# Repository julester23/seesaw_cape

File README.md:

# Seesaw 816 to ULN2308 Darlington
8 GPIOs are routed to a ULN2308. It's an easy way to drive 8 relays (up to 30V).

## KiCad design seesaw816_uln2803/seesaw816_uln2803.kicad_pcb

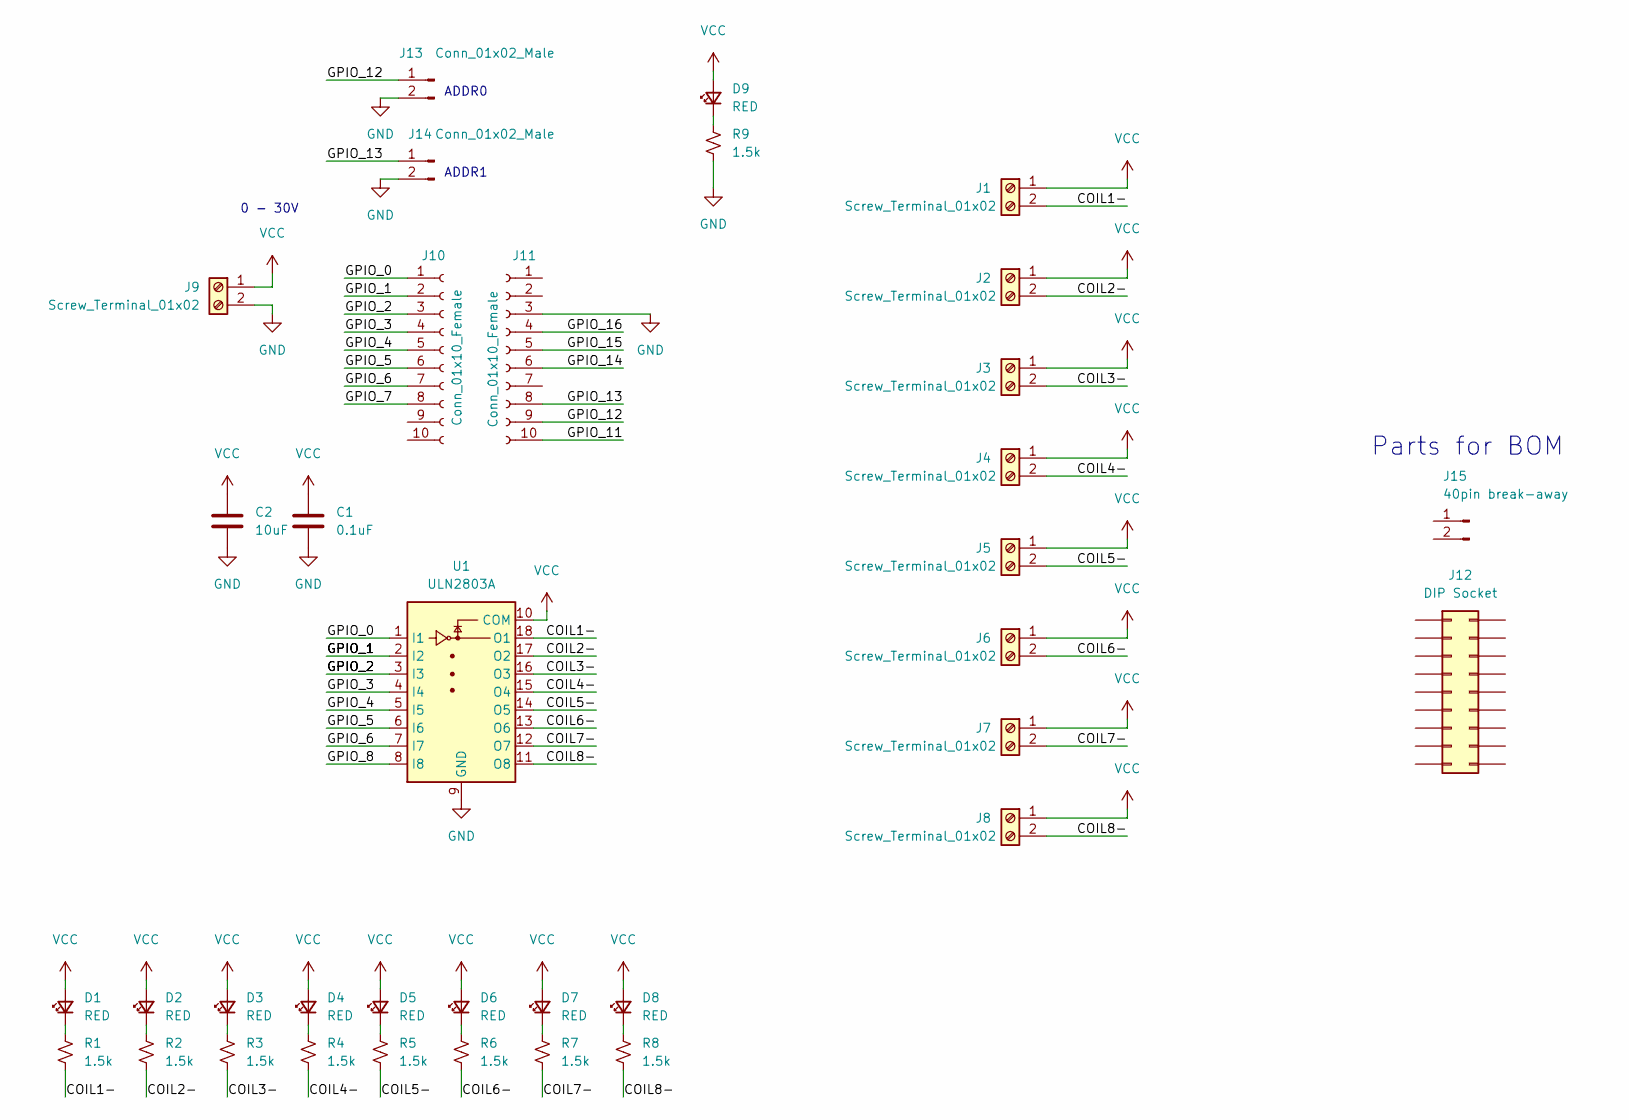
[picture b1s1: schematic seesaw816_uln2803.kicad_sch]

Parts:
C1: 0.1uF; C_0805_2012Metric; Part CC0805KRX7R9BB104
C2: 10uF; CP_Elec_4x5.4; Part EDK106M035A9BAA
D1, D2, D3, D4, D5, D6, D7, D8, D9: RED; LED_0805_2012Metric; Part LS R976-NR-1
J1, J2, J3, J4, J5, J6, J7, J8, J9: Screw_Terminal_01x02; TerminalBlock_TE_282834-2_1x02_P2.54mm_Horizontal
J10, J11: Conn_01x10_Female; PinSocket_1x10_P2.54mm_Vertical
J12: DIP Socket; Part 1-2199298-5
J13, J14: Conn_01x02_Male; PinHeader_1x02_P2.54mm_Vertical
J15: 40pin break-away; Part PRPC040SAAN-RC
R1, R2, R3, R4, R5, R6, R7, R8, R9: 1.5k; R_0805_2012Metric
U1: ULN2803A; DIP-18_W7.62mm_Socket

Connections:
/COIL1-: J1.2, R1.2, U1.18 (O1)
/COIL2-: J2.2, R2.2, U1.17 (O2)
/COIL3-: J3.2, R3.2, U1.16 (O3)
/COIL4-: J4.2, R4.2, U1.15 (O4)
/COIL5-: J5.2, R5.2, U1.14 (O5)
/COIL6-: J6.2, R6.2, U1.13 (O6)
/COIL7-: J7.2, R7.2, U1.12 (O7)
/COIL8-: J8.2, R8.2, U1.11 (O8)
/GPIO_0: J10.1, U1.1 (I1)
/GPIO_1: J10.2, U1.2 (I2)
/GPIO_2: J10.3, U1.3 (I3)
/GPIO_3: J10.4, U1.4 (I4)
/GPIO_4: J10.5, U1.5 (I5)
/GPIO_5: J10.6, U1.6 (I6)
/GPIO_6: J10.7, U1.7 (I7)
/GPIO_7: J10.8
/GPIO_8: U1.8 (I8)
/GPIO_11: J11.10
/GPIO_12: J11.9, J13.1
/GPIO_13: J11.8, J14.1
/GPIO_14: J11.6
/GPIO_15: J11.5
/GPIO_16: J11.4
GND: C1.1, C2.1, J9.2, J11.3, J13.2, J14.2, R9.2, U1.9 (GND)
unnamed: D1.1 (K), R1.1
unnamed: D2.1 (K), R2.1
unnamed: D3.1 (K), R3.1
unnamed: D4.1 (K), R4.1
unnamed: D5.1 (K), R5.1
unnamed: D6.1 (K), R6.1
unnamed: D7.1 (K), R7.1
unnamed: D8.1 (K), R8.1
unnamed: D9.1 (K), R9.1
VCC: C1.2, C2.2, D1.2 (A), D2.2 (A), D3.2 (A), D4.2 (A), D5.2 (A), D6.2 (A), D7.2 (A), D8.2 (A), D9.2 (A), J1.1, J2.1, J3.1, J4.1, J5.1, J6.1, J7.1, J8.1, J9.1, U1.10 (COM)

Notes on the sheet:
0 - 30V
Parts for BOM
ADDR0
ADDR1

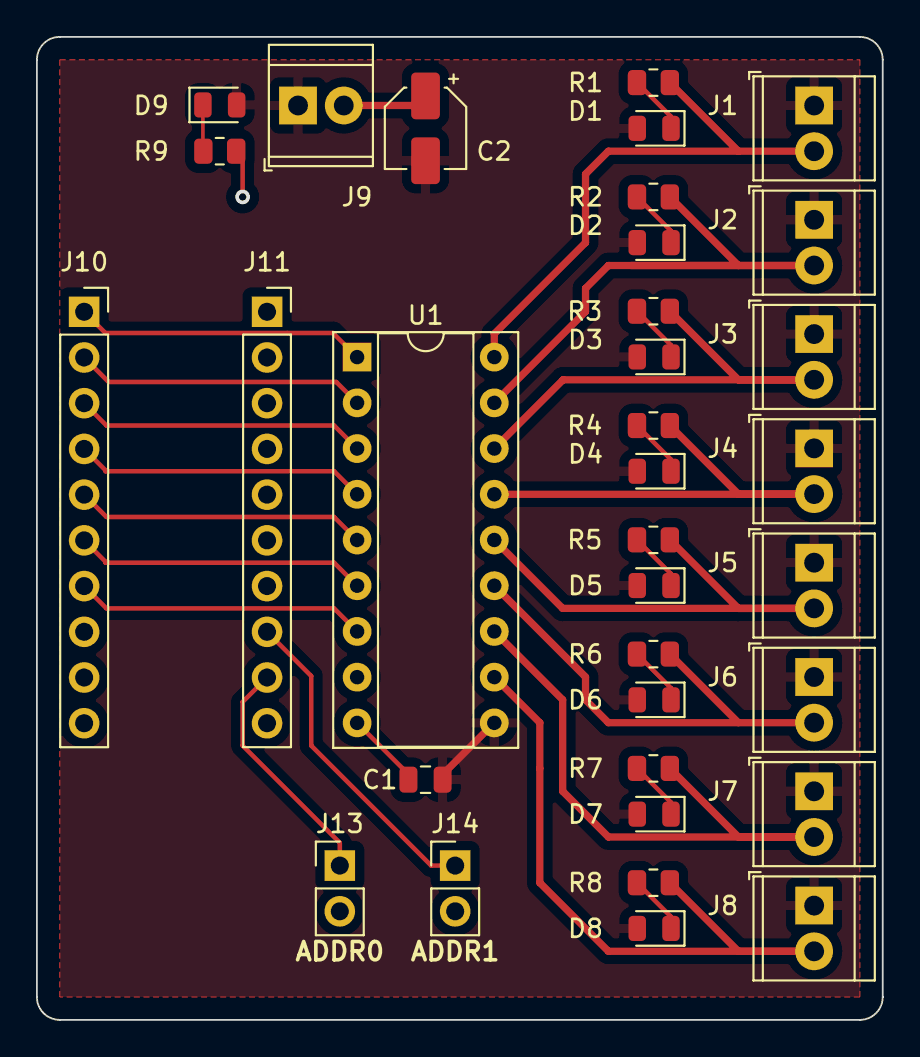
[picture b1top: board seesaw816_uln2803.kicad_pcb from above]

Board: 2 copper layers, 47.0 x 54.6 mm, 34 parts (0 on the bottom side), 28 nets.

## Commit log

2024-01-17 Adding seesaw816 cape
2024-01-17 adding BOM
2024-01-17 adding gerbers
2024-01-17 remove kicad backups
2024-01-20 update to Kicad 7, update BOM
